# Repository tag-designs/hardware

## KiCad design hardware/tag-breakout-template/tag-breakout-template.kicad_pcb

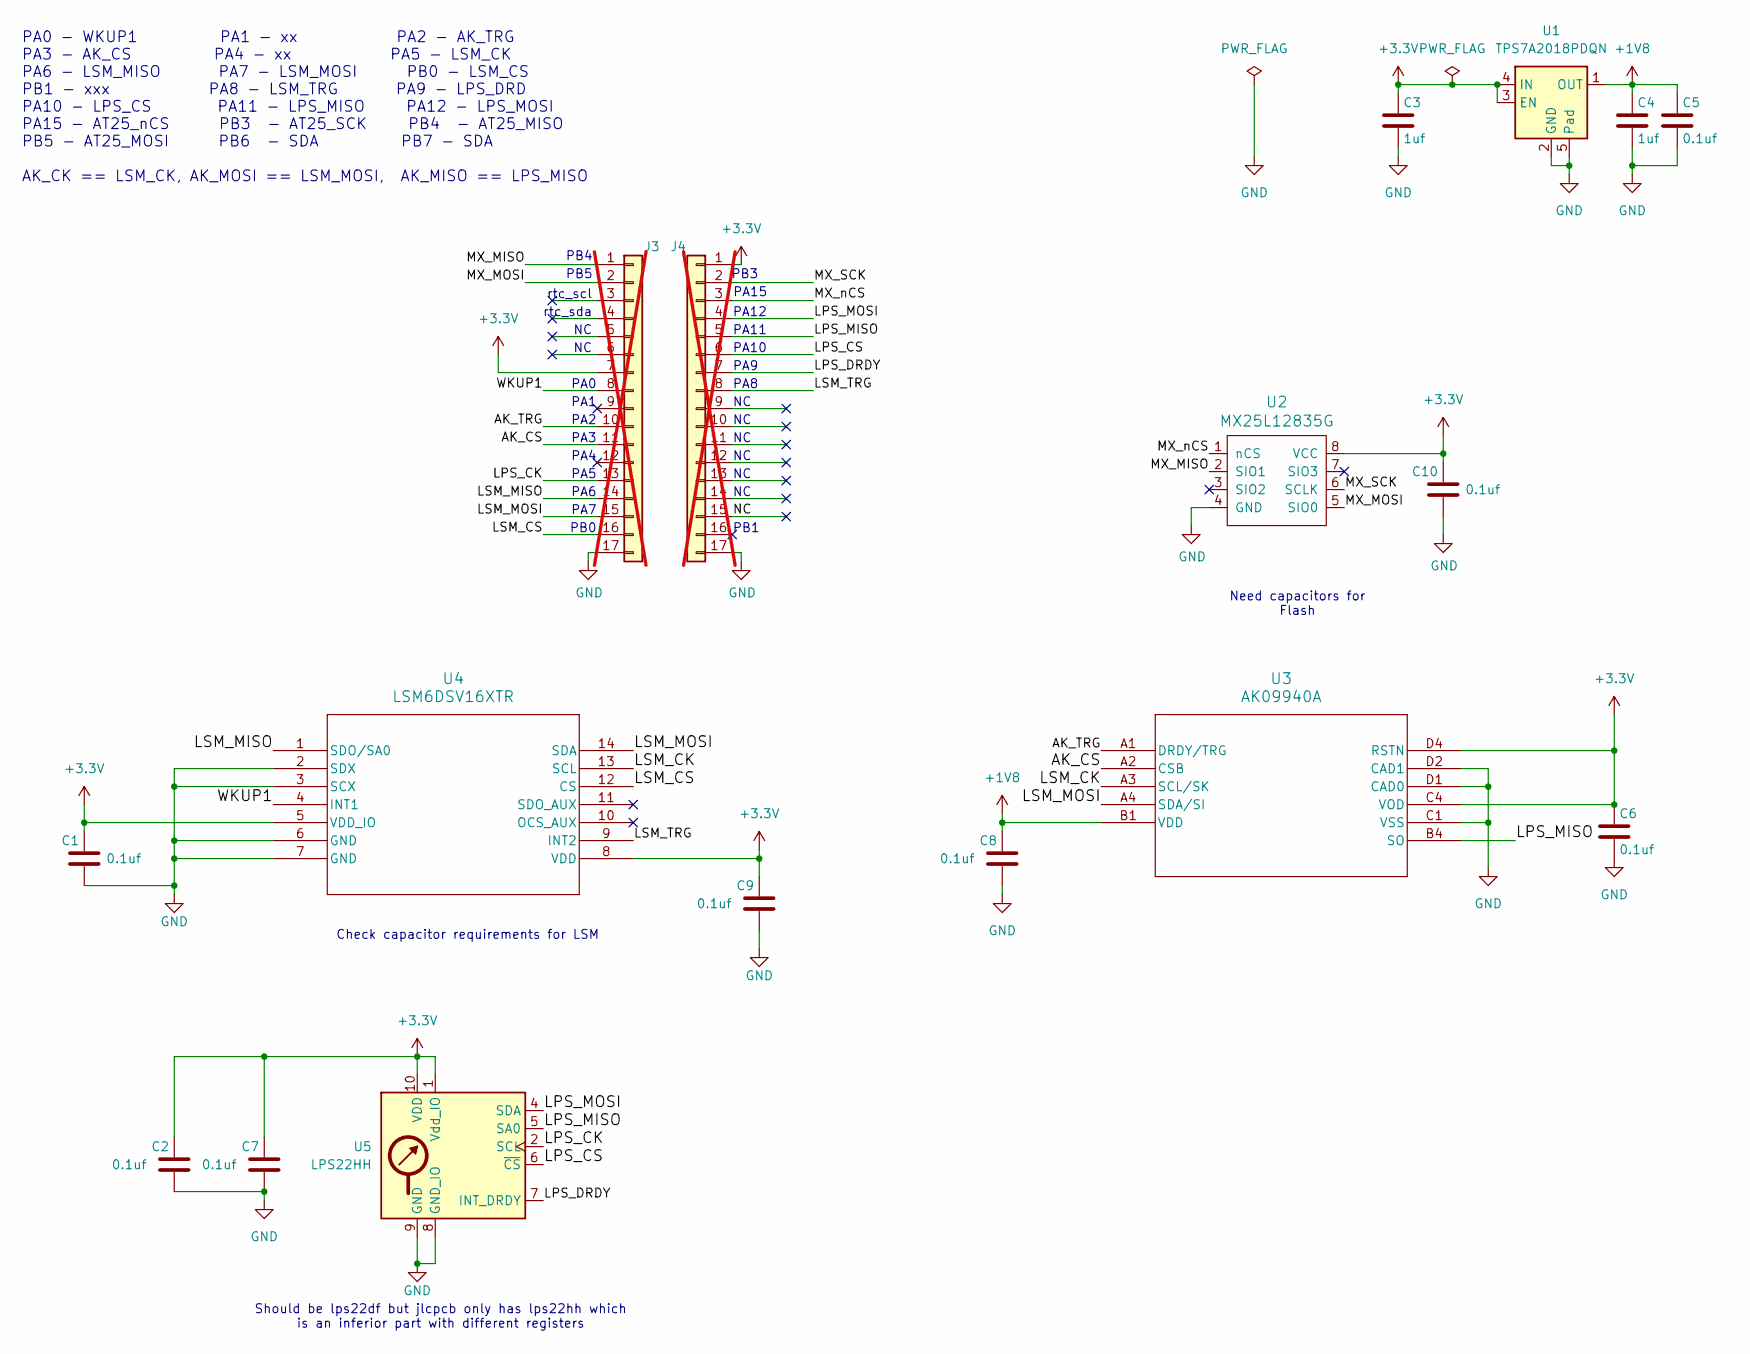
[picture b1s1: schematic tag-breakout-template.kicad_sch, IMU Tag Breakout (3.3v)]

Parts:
C1, C2, C5, C6, C7, C8, C9, C10: 0.1uf; C_0603_1608Metric; MPN CC0603KRX7R9BB104; LCSC C14663
C3, C4: 1uf; C_0603_1608Metric; MPN CL10A105KB8NNNC; LCSC C15849
J3, J4: Conn_01x17; PinHeader_1x17_P2.54mm_Vertical_Staggered; not fitted
U1: TPS7A2018PDQN; Texas_X2SON-4_1x1mm_P0.65mm; MPN TPS7A2018PDQNR; LCSC C2878130
U2: MX25L12835G; SOIC-8_5.3x6.2mm_P1.27mm; MPN MX25L12845GM2I-08G-TR; LCSC C136615
U3: AK09940A; AK09940a; MPN AK09940A; LCSC C6794828
U4: LSM6DSV16XTR; LGA-14_3x2.5mm_P0.5mm_LayoutBorder3x4y; MPN LSM6DSV; LCSC C5267406
U5: LPS22HH; ST_HLGA-10_2x2mm_P0.5mm_LayoutBorder3x2y; MPN LPS22HH; LCSC C2827824

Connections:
+1V8: C4.1, C5.1, C8.1, U1.1 (OUT), U3.B1 (VDD)
+3.3V: C1.1, C2.1, C3.1, C6.1, C7.1, C9.1, C10.1, J3.7, J4.1, U1.3 (EN), U1.4 (IN), U2.8 (VCC), U3.C4 (VOD), U3.D4 (RSTN), U4.5 (VDD_IO), U4.8 (VDD), U5.1 (Vdd_IO), U5.10 (VDD)
/AK_CS: J3.11, U3.A2 (CSB)
/AK_TRG: J3.10, U3.A1 (DRDY/TRG)
/LPS_CK: J3.13, U5.2 (SCL)
/LPS_CS: J4.6, U5.6 (~CS)
/LPS_DRDY: J4.7, U5.7 (INT_DRDY)
/LPS_MISO: J4.5, U3.B4 (SO), U5.5 (SA0)
/LPS_MOSI: J4.4, U5.4 (SDA)
/LSM_CK: U3.A3 (SCL/SK), U4.13 (SCL)
/LSM_CS: J3.16, U4.12 (CS)
/LSM_MISO: J3.14, U4.1 (SDO/SA0)
/LSM_MOSI: J3.15, U3.A4 (SDA/SI), U4.14 (SDA)
/LSM_TRG: J4.8, U4.9 (INT2)
/MX_MISO: J3.1, U2.2 (SIO1)
/MX_MOSI: J3.2, U2.5 (SIO0)
/MX_SCK: J4.2, U2.6 (SCLK)
/MX_nCS: J4.3, U2.1 (nCS)
/NC: J4.15
/WKUP1: J3.8, U4.4 (INT1)
GND: C1.2, C2.2, C3.2, C4.2, C5.2, C6.2, C7.2, C8.2, C9.2, C10.2, J3.17, J4.17, U1.2 (GND), U1.5 (Pad), U2.4 (GND), U3.C1 (VSS), U3.D1 (CAD0), U3.D2 (CAD1), U4.2 (SDX), U4.3 (SCX), U4.6 (GND), U4.7 (GND), U5.3 (GND), U5.8 (GND_IO), U5.9 (GND)

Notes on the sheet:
PA1
PA9
PA2
PA0
PA8
PA7
PA15
PA5
PA4
PB3
Need capacitors for Flash
PA6
Should be lps22df but jlcpcb only has lps22hh which is an inferior part with different registers
PA3
PB4
PA12
PB0
PA0 - WKUP1 PA1 - xx PA2 - AK_TRG PA3 - AK_CS PA4 - xx PA5 - LSM_CK PA6 - LSM_MISO PA7 - LSM_MOSI PB0 - LSM_CS PB1 - xxx PA8 - LSM_TRG PA9 - LPS_DRD PA10 - LPS_CS PA11 - LPS_MISO PA12 - LPS_MOSI PA15 - AT25_nCS PB3 - AT25_SCK PB4 - AT25_MISO PB5 - AT25_MOSI PB6 - SDA PB7 - SDA AK_CK == LSM_CK, AK_M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
PB5
Check capacitor requirements for LSM
PA10
rtc_sda
PA11
PB1
rtc_scl

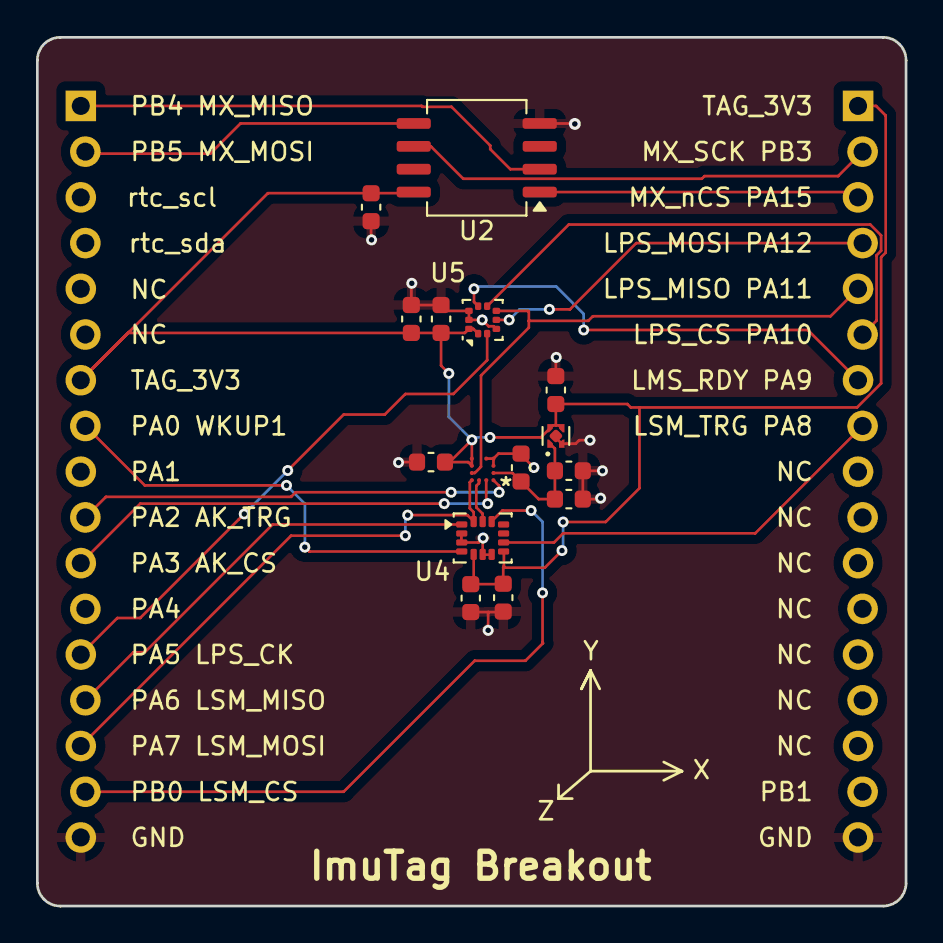
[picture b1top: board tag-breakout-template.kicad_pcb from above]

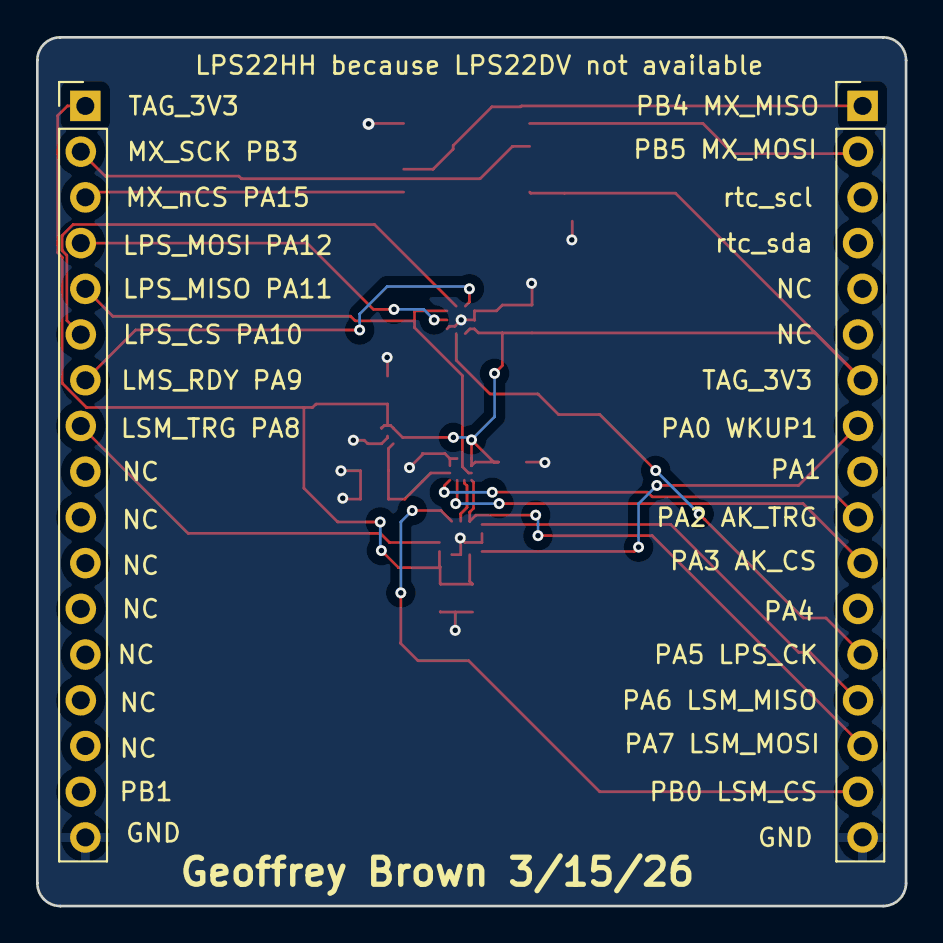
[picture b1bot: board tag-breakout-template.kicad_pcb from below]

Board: 2 copper layers, 48.3 x 48.3 mm, 17 parts (2 on the bottom side), 20 nets.

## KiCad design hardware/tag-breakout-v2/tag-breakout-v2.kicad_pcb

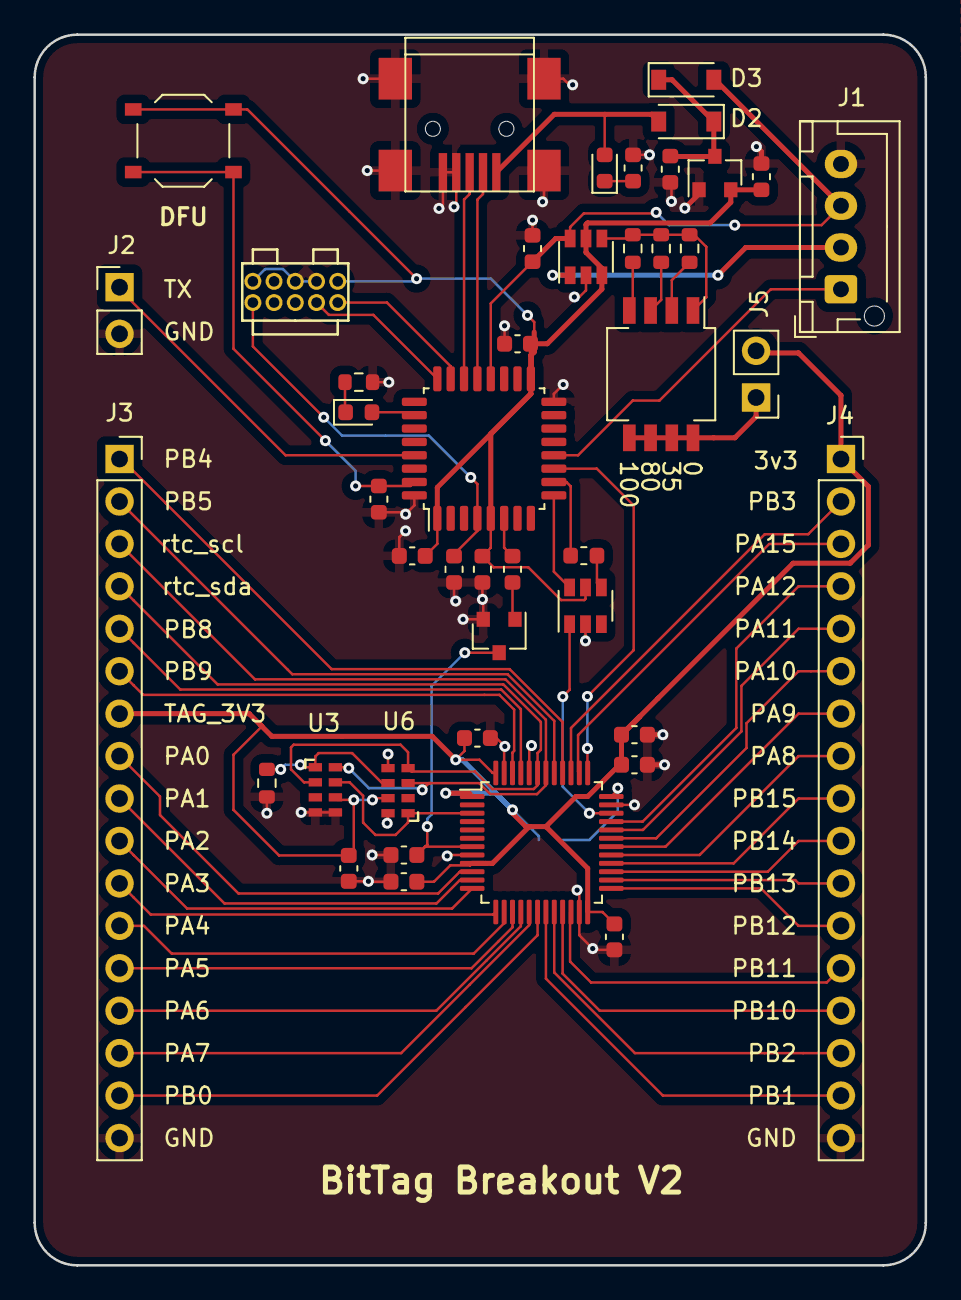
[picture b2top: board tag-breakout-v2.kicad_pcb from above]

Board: 2 copper layers, 53.3 x 73.7 mm, 45 parts (1 on the bottom side), 64 nets.

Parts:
C1, C104: 1uF; C_0603_1608Metric
C2, C3, C4, C5, C6, C7, C9, C11, C101, C107: 0.1uF; C_0603_1608Metric
C10: 4.7uF; C_0603_1608Metric
D1: LED-GREEN; LED_0603_1608Metric
D2, D3: D_Schottky; D_SOD-123
D105: LED-RED; LED_0603_1608Metric
J1: Conn_01x04_Female; JST_XH_B04B-XH-AM_1x04_P2.50mm_Vertical
J2, J5: Conn_01x02_Male; PinHeader_1x02_P2.54mm_Vertical
J3, J4: Conn_01x17; PinSocket_1x17_P2.54mm_Vertical
J102: Conn_02x05_Odd_Even; FTSH-105-01-F-D-K
J104: USB_B_Mini; USB_Mini-B
JP1: SolderJumper_2_Open; SolderJumper-2_P1.3mm_Open_TrianglePad1.0x1.5mm
Q1: Q_NPN_BEC; SOT-23
R1, R107: 620; R_0603_1608Metric
R2: 36; R_0603_1608Metric
R3, R105: 10K; R_0603_1608Metric
R4, R104: 2.2K; R_0603_1608Metric
R5: 82; R_0603_1608Metric
R6, R106: 100; R_0603_1608Metric
SW1: SW_DIP_x04; SW_DIP_SPSTx04_Slide_Copal_CHS-04B_W7.62mm_P1.27mm
U1: XC6206; SOT-23
U2, U4: TS5A3159ADBVR; SOT-23-6
U3: RV-3032-C7; RV-8803-C7
U6: RV-3028-C7; RV-8803-C7
U7: STM32L431CCTx; LQFP-48_7x7mm_P0.5mm
U101: STM32F042K6Tx; LQFP-32_7x7mm_P0.8mm
U105: Tactile Switch; SW_SPST_TS_1187

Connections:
+3V3: C2.1, C11.1, C104.1, C107.1, J102.1, U1.2, U2.5, U4.3, U4.5, U101.1, U101.5, U101.17, U105.2
/LED_GREEN: D1.2, U101.26
/NRST: C101.1, J102.10, U101.4
/SCLK: J102.4, U101.24
/SWDIO: J102.2, U101.23
/UART_TX: J2.1, U101.29
/USB_DM: J104.2, U101.21
/USB_DP: J104.3, U101.22
/boot0: R105.2, U101.31, U105.1
/stm32/NRST: C5.1, Q1.3, U7.7
/stm32/PA0: J3.8, U7.10
/stm32/PA1: J3.9, U7.11
/stm32/PA2: J3.10, U7.12
/stm32/PA3: J3.11, U7.13
/stm32/PA4: J3.12, U7.14
/stm32/PA5: J3.13, U7.15
/stm32/PA6: J3.14, U7.16
/stm32/PA7: J3.15, U7.17
/stm32/PA8: J4.8, U7.29
/stm32/PA9: J4.7, U7.30
/stm32/PA10: J4.6, U7.31
/stm32/PA11: J4.5, U7.32
/stm32/PA12: J4.4, U7.33
/stm32/PA15: J4.3, U7.38
/stm32/PB0: J3.16, U7.18
/stm32/PB1: J4.16, U7.19
/stm32/PB2: J4.15, U7.20
/stm32/PB3: J4.2, U7.39
/stm32/PB4: J3.1, U7.40
/stm32/PB5: J3.2, U7.41
/stm32/PB8: J3.5, U7.45
/stm32/PB9: J3.6, U7.46
/stm32/PB10: J4.14, U7.21
/stm32/PB11: J4.13, U7.22
/stm32/PB12: J4.12, U7.25
/stm32/PB13: J4.11, U7.26
/stm32/PB14: J4.10, U7.27
/stm32/PB15: J4.9, U7.28
/stm32/TAG_PWR: C3.1, C4.1, C6.1, C7.1, C9.1, C10.1, J3.7, J4.1, J5.2, JP1.1, U3.6, U6.7, U7.1, U7.9, U7.24, U7.48
/stm32/VBACK: R3.2, U3.1, U6.6
/stm32/clkout: U3.7, U6.1, U7.3
/stm32/rtc_scl: J3.3, U3.8, U6.3, U7.42
/stm32/rtc_sda: J3.4, U3.2, U6.4, U7.43
EXT_PWR: D3.2, J1.3, R4.1, U4.6, U101.20
GND: C1.2, C2.2, C3.2, C4.2, C5.2, C6.2, C7.2, C9.2, C10.2, C11.2, C101.2, C104.2, C107.2, J1.4, J2.2, J3.17, J4.17, J102.3, J102.5, J102.9, J104.4, J104.5, J104.6, Q1.2, R1.2, R3.1, R4.2, R105.1, R107.2, U1.1, U2.2, U3.4, U3.5, U4.2, U6.5, U6.8, U7.8, U7.23, U7.35, U7.44, U7.47, U101.16, U101.32
unnamed: C1.1, D2.1, D3.1, U1.3
unnamed: D1.1, R1.1
unnamed: D105.1, R107.1
unnamed: JP1.2, U7.36
unnamed: R2.1, SW1.2
unnamed: R2.2, R5.2, R6.2, SW1.1, U4.4
unnamed: R5.1, SW1.3
unnamed: R6.1, SW1.4
unnamed: R104.2, U101.6
unnamed: R106.1, U101.10
unnamed: R106.2, U2.4
unnamed: U2.6, U101.9
PWR_IN: J1.2, U4.1
PWR_IN_MIRROR: J1.1, U101.12
TAG_3V3: J5.1, SW1.5, SW1.6, SW1.7, SW1.8
TAG_RESET: Q1.1, R104.1
TAG_SCK: U7.37, U101.11
TAG_SWDIO: U2.1, U7.34
VUSB: D2.2, D105.2, J104.1

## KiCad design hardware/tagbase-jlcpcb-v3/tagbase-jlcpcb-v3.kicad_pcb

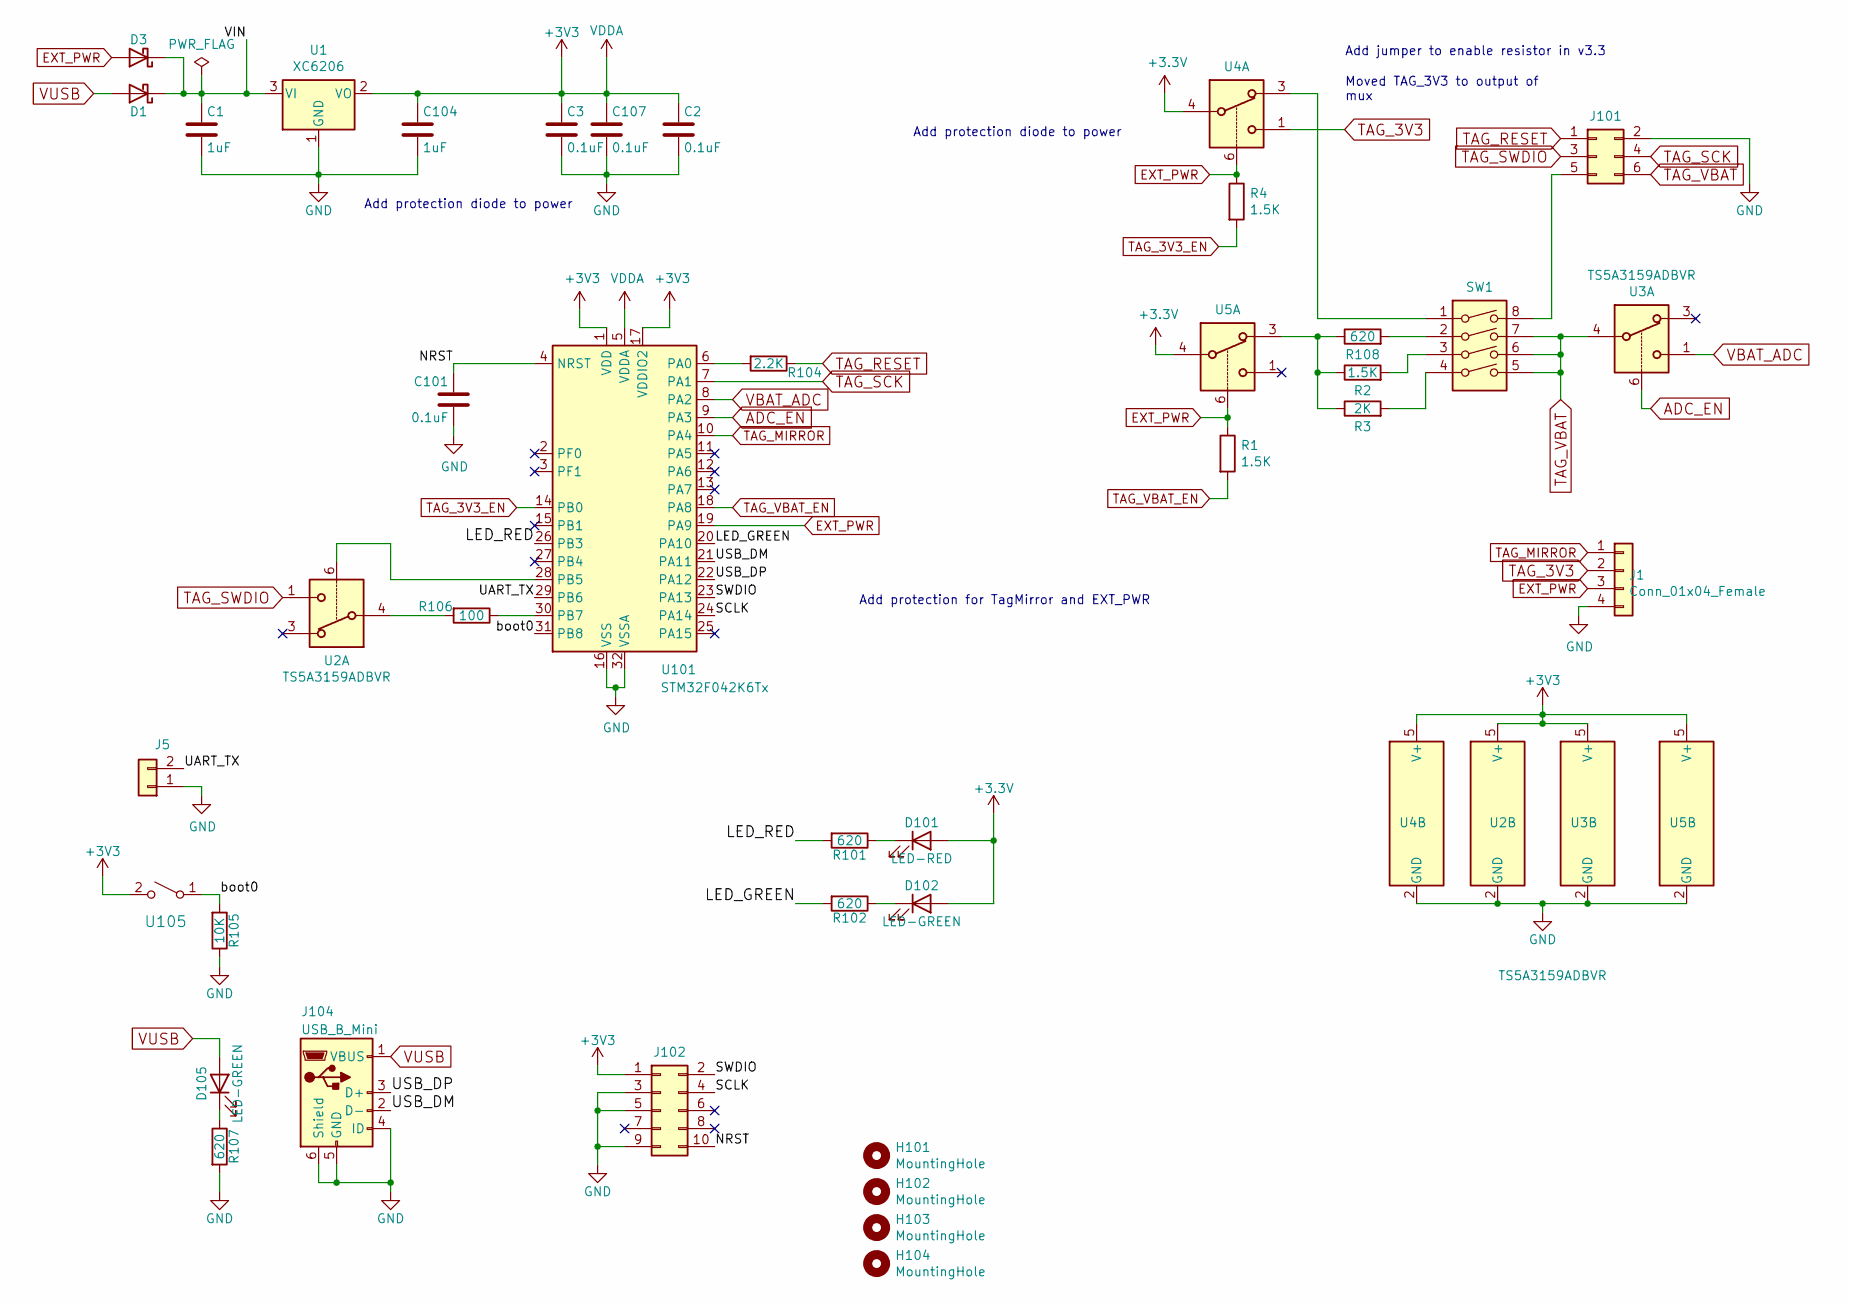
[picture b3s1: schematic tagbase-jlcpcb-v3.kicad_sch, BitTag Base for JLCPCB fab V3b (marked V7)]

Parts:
C1, C104: 1uF; C_0603_1608Metric; MPN CL10A105KB8NNNC; LCSC C15849
C2, C3, C101, C107: 0.1uF; C_0603_1608Metric; MPN CC0603KRX7R9BB104; LCSC C14663
D1, D3: DIODE; D_SOD-123; MPN B5819W; LCSC C8598
D101: LED-RED; LED_0603_1608Metric; MPN KT-0603R; LCSC C2286
D102, D105: LED-GREEN; LED_0603_1608Metric; MPN 19-217/GHC-YR1S2/3T; LCSC C72043
H101, H102, H103, H104: MountingHole; MountingHole_3.2mm_M3
J1: Conn_01x04_Female; JST_XH_B04B-XH-AM_1x04_P2.50mm_Vertical
J5: Conn_01x02; PinHeader_1x02_P2.54mm_Vertical
J101: Conn_02x03_Odd_Even; 6pin_tagpoints_new_offset
J102: Conn_02x05_Odd_Even; FTSH-105-01-F-D-K
J104: USB_B_Mini; USB_Mini-B; MPN 690-005-299-043
R1, R2, R4: 1.5K; R_0603_1608Metric; MPN 0603WAF1501T5E; LCSC C22843
R3: 2K; R_0603_1608Metric; MPN 0603WAF2001T5E; LCSC C22975
R101, R102, R107, R108: 620; R_0603_1608Metric; MPN 0603WAF6200T5E; LCSC C23220
R104: 2.2K; R_0603_1608Metric; MPN 0603WAF1002T5E; LCSC C4190
R105: 10K; R_0603_1608Metric; MPN 0603WAF1002T5E; LCSC C25804
R106: 100; R_0603_1608Metric; MPN 0603WAF1000T5E; LCSC C22775
SW1: SW_DIP_x04; SW_DIP_SPSTx04_Slide_KingTek_DSHP04TS_W7.62mm_P1.27mm; MPN 218-4LPSTR
U1: XC6206; SOT-23; MPN XC6206P332MR; LCSC C5446
U2, U3, U4, U5: TS5A3159ADBVR; SOT-23-6; MPN TS5A3159ADBVR; LCSC C128405
U101: STM32F042K6Tx; LQFP-32_7x7mm_P0.8mm; LCSC C69216
U105: Tactile Switch; SW_SPST_TS_1187; MPN TS-1187A-C-E-B; LCSC C318889

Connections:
/LED_GREEN: R102.2, U101.20 (PA10)
/LED_RED: R101.2, U101.26 (PB3)
/NRST: C101.1, J102.10, U101.4 (NRST)
/SCLK: J102.4, U101.24 (PA14)
/SWDIO: J102.2, U101.23 (PA13)
/UART_TX: J5.2, U101.29 (PB6)
/USB_DM: J104.2 (D-), U101.21 (PA11)
/USB_DP: J104.3 (D+), U101.22 (PA12)
/VIN: C1.1, D1.1 (K), D3.1 (K), U1.3 (VI)
/boot0: R105.2, U101.31 (PB8), U105.1 (A)
ADC_EN: U3.6, U101.9 (PA3)
EXT_PWR: D3.2 (A), J1.3, R1.1, R4.1, U4.6, U5.6, U101.19 (PA9)
GND: C1.2, C2.2, C3.2, C101.2, C104.2, C107.2, J1.4, J5.1, J101.2, J102.3, J102.5, J102.9, J104.4 (ID), J104.5 (GND), J104.6 (Shield), R105.1, R107.2, U1.1 (GND), U2.2 (GND), U3.2 (GND), U4.2 (GND), U5.2 (GND), U101.16 (VSS), U101.32 (VSSA)
unnamed: D101.1 (K), R101.1
unnamed: D102.1 (K), R102.1
unnamed: D105.1 (K), R107.1
unnamed: J101.5, SW1.8
unnamed: R2.2, SW1.3
unnamed: R3.2, SW1.4
unnamed: R104.2, U101.6 (PA0)
unnamed: R106.1, U101.30 (PB7)
unnamed: R106.2, U2.4
unnamed: R2.1, R3.1, R108.1, U5.3
unnamed: R108.2, SW1.2
unnamed: SW1.1, U4.3
unnamed: U2.6, U101.28 (PB5)
TAG_3V3: J1.2, U4.1
TAG_3V3_EN: R4.2, U101.14 (PB0)
TAG_MIRROR: J1.1, U101.10 (PA4)
TAG_RESET: J101.1, R104.1
TAG_SCK: J101.4, U101.7 (PA1)
TAG_SWDIO: J101.3, U2.1
TAG_VBAT: J101.6, SW1.5, SW1.6, SW1.7, U3.4
TAG_VBAT_EN: R1.2, U101.18 (PA8)
VBAT_ADC: U3.1, U101.8 (PA2)
VUSB: D1.2 (A), D105.2 (A), J104.1 (VBUS)

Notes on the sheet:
Moved TAG_3V3 to output of mux
Add protection for TagMirror and EXT_PWR
Add protection diode to power
Add jumper to enable resistor in v3.3

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
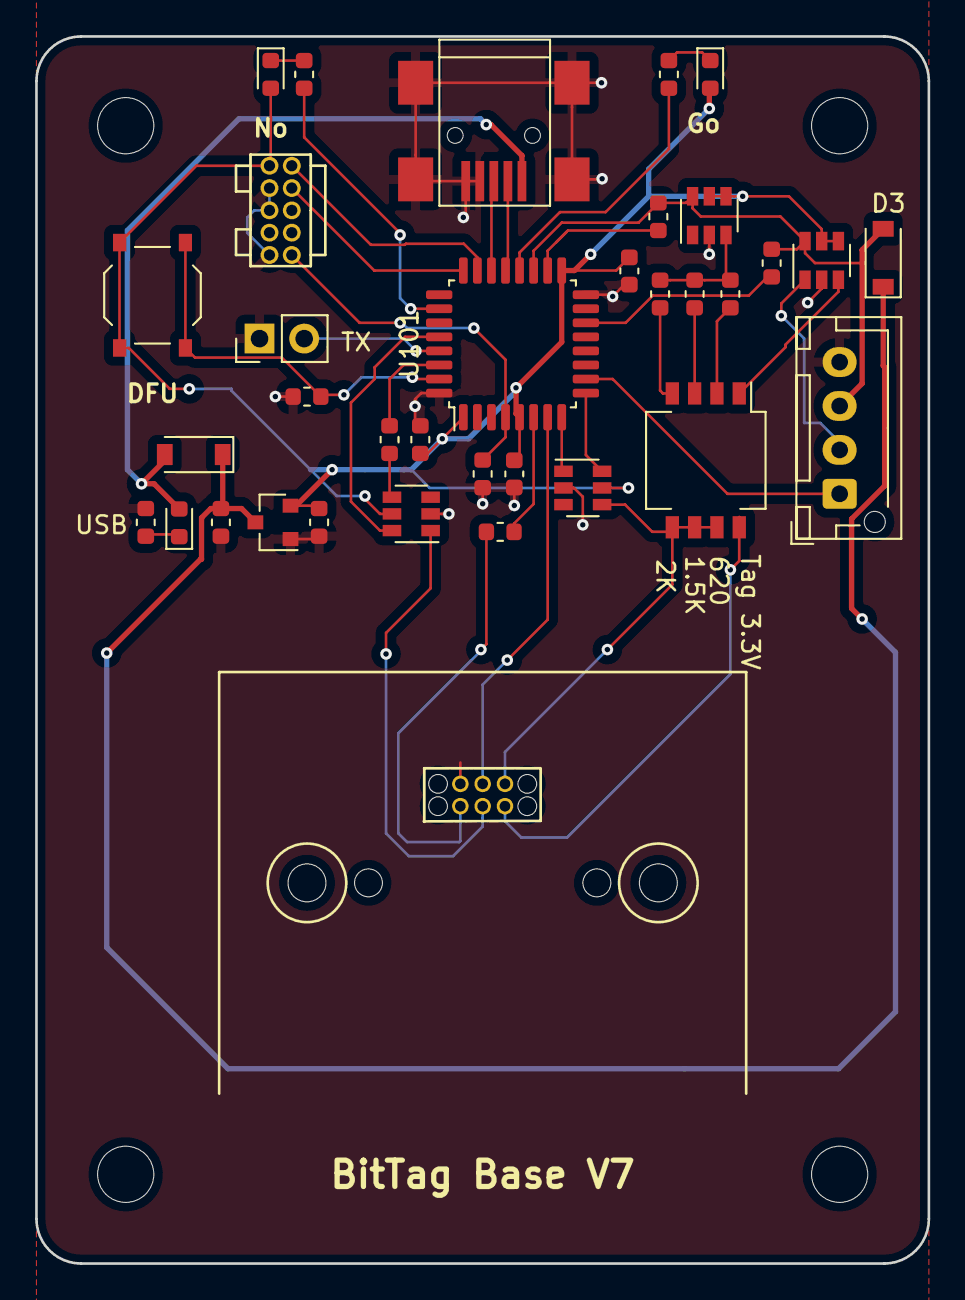
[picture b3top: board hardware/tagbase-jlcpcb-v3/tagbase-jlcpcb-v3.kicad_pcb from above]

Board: 2 copper layers, 50.8 x 69.9 mm, 39 parts (0 on the bottom side), 37 nets.

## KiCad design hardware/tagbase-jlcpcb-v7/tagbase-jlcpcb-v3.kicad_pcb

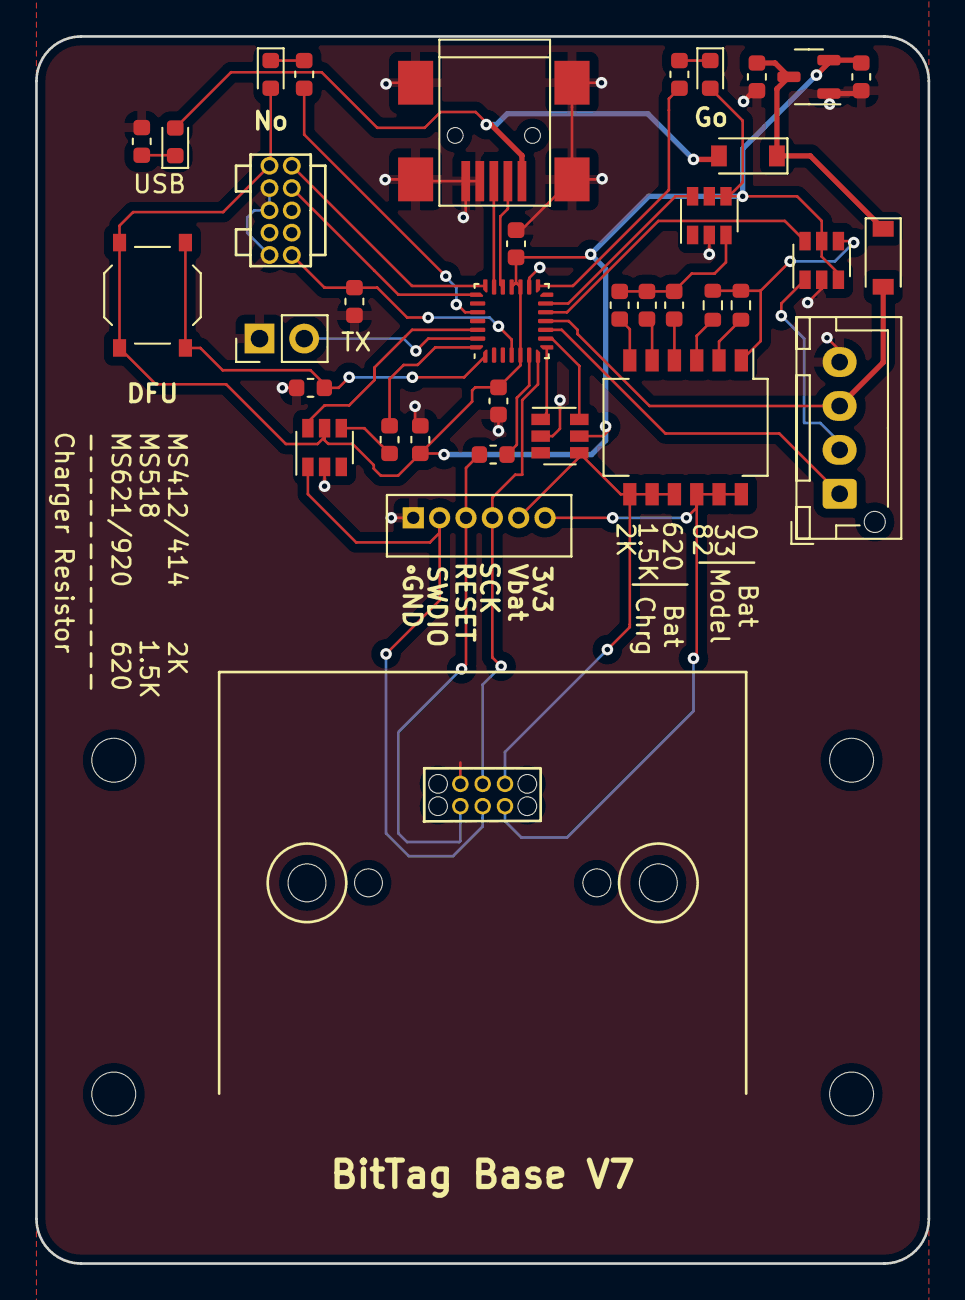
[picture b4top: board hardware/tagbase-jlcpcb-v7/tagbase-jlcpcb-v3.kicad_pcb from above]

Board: 2 copper layers, 50.8 x 69.9 mm, 40 parts (0 on the bottom side), 39 nets.

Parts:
C1, C104: 1uF; C_0603_1608Metric
C2, C3, C101, C107: 0.1uF; C_0603_1608Metric
D1, D3: DIODE; D_SOD-123
D101: LED-RED; LED_0603_1608Metric
D102, D105: LED-GREEN; LED_0603_1608Metric
H1, H2, H3, H4: MountingHole; MountingHole_2.5mm
J1: Conn_01x04_Female; JST_XH_B04B-XH-AM_1x04_P2.50mm_Vertical
J2: Conn_01x06; JST_B6B-ZR(LF)(SN)
J5: Conn_01x02; PinHeader_1x02_P2.54mm_Vertical
J101: Conn_02x03_Odd_Even; 6pin_tagpoints_new_offset
J102: Conn_02x05_Odd_Even; FTSH-105-01-F-D-K
J104: USB_B_Mini; USB_Mini-B
R2: 1.5K; R_0603_1608Metric
R3: 2K; R_0603_1608Metric
R5: 33; R_0603_1608Metric
R6: 82; R_0603_1608Metric
R101, R102, R107, R108: 620; R_0603_1608Metric
R104: 2.2K; R_0603_1608Metric
R105: 10K; R_0603_1608Metric
R106: 100; R_0603_1608Metric
SW1: SW_DIP_x04; SW_DIP_SPSTx06_Slide_KingTek_DSHP06TS_W7.62mm_P1.27mm
U1: XC6206; SOT-23-3
U2, U3, U4, U5: TS5A3159ADBVR; SOT-23-6
U6: STM32F042G6Ux; QFN-28_4x4mm_P0.5mm
U105: Tactile Switch; SW_SPST_TS_1187

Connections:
+3V3: C2.1, C3.1, C104.1, C107.1, D101.2 (A), D102.2 (A), J102.1, U1.2 (VO), U2.5 (V+), U3.5 (V+), U4.3, U4.5 (V+), U5.4, U5.5 (V+), U6.5 (VDDA), U6.17 (VDD), U6.18 (VDDIO2), U105.2 (B)
/LED_GREEN: R102.2, U6.15 (PB1)
/LED_RED: R101.2, U6.24 (PB3)
/NRST: C101.1, J102.10, U6.4 (NRST)
/SCLK: J102.4, U6.22 (PA14)
/SWDIO: J102.2, U6.21 (PA13)
/TAG_SWDIO_EN: U2.6, U6.26 (PB5)
/UART_TX: J5.2, U6.27 (PB6)
/USB_DM: J104.2 (D-), U6.19 (PA9/PA11)
/USB_DP: J104.3 (D+), U6.20 (PA10/PA12)
/VIN: C1.1, D1.1 (K), D3.1 (K), U1.3 (VI)
/boot0: R105.2, U6.1 (PB8), U105.1 (A)
ADC_EN: U3.6, U6.9 (PA3)
EXT_PWR: D3.2 (A), J1.3, U6.11 (PA5)
GND: C1.2, C2.2, C3.2, C101.2, C104.2, C107.2, J1.4, J2.1, J5.1, J101.2, J102.3, J102.5, J102.9, J104.4 (ID), J104.5 (GND), J104.6 (Shield), R105.1, R107.2, U1.1 (GND), U2.2 (GND), U3.2 (GND), U4.2 (GND), U5.2 (GND), U6.16 (VSSA)
unnamed: D101.1 (K), R101.1
unnamed: D102.1 (K), R102.1
unnamed: D105.1 (K), R107.1
unnamed: R2.2, SW1.5
unnamed: R3.2, SW1.6
unnamed: R5.1, R6.2, SW1.1, U4.4
unnamed: R5.2, SW1.2
unnamed: R6.1, SW1.3
unnamed: R104.2, U6.6 (PA0)
unnamed: R106.1, U6.28 (PB7)
unnamed: R106.2, U2.4
unnamed: R2.1, R3.1, R108.1, U5.3
unnamed: R108.2, SW1.4
TAG_3V3: J2.6, J101.5, SW1.10, SW1.11, SW1.12
TAG_3V3_EN: U4.6, U6.12 (PA6)
TAG_3V3_IN: J1.2, U4.1
TAG_MIRROR: J1.1, U6.10 (PA4)
TAG_RESET: J2.3, J101.1, R104.1
TAG_SCK: J2.4, J101.4, U6.7 (PA1)
TAG_SWDIO: J2.2, J101.3, U2.1
TAG_VBAT: J2.5, J101.6, SW1.7, SW1.8, SW1.9, U3.4
VBAT_ADC: U3.1, U6.8 (PA2)
VUSB: D1.2 (A), D105.2 (A), J104.1 (VBUS)
~TAG_VBAT_EN: U5.6, U6.13 (PA7)
